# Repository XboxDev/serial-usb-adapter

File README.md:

# Original Xbox Serial USB Adapter

This device allows for serial communication with an original Xbox and is primarily used for kernel debugging.

For questions or support, contact xbox7887 in the [XboxDev on Discord](https://discord.gg/WxJPPyz).

## Requirements

### Hardware

Any original Xbox of any version (although versions 1.3-1.5 require LFRAME# reconnect and version 1.6 requires full LPC port rebuild, including LFRAME#).
Debug and development kits will work without modification, however, retail boxes need to use a hacked kernel (X2 5035 or Cerbios for example) that initializes superio as well as have a 2x8 2.54mm pin header soldered to the LPC port.

### Software

A Windows OS capable of running WinDbg; versions 4.0.0018.0 (XDK) or [6.12.0002.633](http://download.microsoft.com/download/A/6/A/A6AC035D-DA3F-4F0C-ADA4-37C8E5D34E3D/setup/WinSDKDebuggingTools/dbg_x86.msi) have been tested successfully.

Optionally, [KiCad 7.0](http://kicad-pcb.org/download/) if you need to work with the PCB project files.

### BIOS Compatibility

   - Cerbios - use on any board
   - X2 4979 BFM - use on any board
   - X2 4981 (256 KB) - use on 1.2+ boards
   - X2 4983 BFM - use on any board
   - X2 5035 (512 KB) - use on 1.0-1.1 boards

## Usage

Connect a USB-C cable from your PC to the serial adapter, then the IDC cable ends into the serial adapter and Xbox LPC port pin headers respectively, ensuring the correct alignment and orientation as shown in the image above. **Incorrect orientation may result in damage to the adapter and/or your Xbox, you have been warned!**

Within WinDbg press `CTRL+K` to bring up the connection dialog and enter `115200` for the baud rate along with the `COM#` port as detected by your computer in device manager.

`CTRL+Break` can be used to pause execution, `F5` to continue, and `F10/F11` to step over or through instructions.
`CTRL+ALT+D` will toggle verbose windbg protocol output for troubleshooting if needed.
The adapter's blue RX LED indicates signals sent from the PC and the green TX LED from the Xbox. 

## Components

Bold designators are the bare minimum required for basic functionality but stability may be questionable. The entire UART to USB circuit and/or LED output is optional and can be replaced with an external 3.3V UART to USB cable jumpered to J2 instead.

| Count | Part/Value | Description | Designators | Notes |
| - | - | - | - | - |
| 1  | 2x8 2.54mm | Pin Header | **JP1** | |
| 1  | Stewart SS-52400-003 | USB-C Connector  | **J1** | |
| 1  | 1x3 2.54mm | Pin Header | J2 | Optional UART breakout |
| 1  | SG5032CAN | 14.318MHz 5032 Crystal Oscillator | **Y1** | |
| 1  | LPC47M192 | SuperIO | **U1** | The LPC47M157 is also compatible |
| 1  | FT231XS | UART to USB | **U2** | |
| 2  | 27R | 0603 SMD Resistor | **R1**, **R3** | Filtering |
| 2  | 10k | 0603 SMD Resistor | **R2**, **R4** | Configuration pull-ups/downs |
| 1  | 470R | 0603 SMD Resistor | R5 | LED power dissipation |
| 1  | 1.2k | 0603 SMD Resistor | R6 | LED power dissipation  |
| 2  | 5.1k | 0603 SMD Resistor | **R7**, **R8** | USB-C Configuration pull-downs |
| 2  | 100R | 4x0603 SMD Resistor Network | **RN1**, **RN2** | Terminating resistors for longer LPC ribbons (10+ inches) |
| 1  | 33 Ohm | 0603 Ferrite Bead | **FB1** | Filtering, can be substituted with a 0 ohm resistor or solder bridge |
| 3  | 47pF | 0603 SMD Capacitor | C6, C7 | Filtering |
| 6  | 10nF | 0603 SMD Capacitor | C3, **C8**, C9, **C10**, C12, C13 | Decoupling |
| 2  | 100nF | 0603 SMD Capacitor | C2, C11 | Decoupling |
| 1  | 4.7uF | 0603 SMD Capacitor | C1 | Bulk |
| 1  | 10uF | 0603 SMD Capacitor | C5 | Bulk |
| 1  | Green | 0603 SMD LED | D1 | |
| 1  | Blue | 0603 SMD LED | D2 | |

### External Components

| Count | Part/Value | Description | Designators | Notes |
| - | - | - | - | - |
| 1 | 2x8 2.54mm | Pin Header | N/A | Retail Xbox LPC Connector |
| 1 | 16 Wire 2.54mm | Female to Female IDC Ribbon Cable | N/A | Keep length under 18 inches for best results |
| 1 | USB-C Cable | Cable | N/A | |

### Component Retailers

* [Mouser](https://www.mouser.com/)
* [Digi-Key](https://www.digikey.com/)
* [Arrow](https://www.arrow.com/)
* [Utsource](https://www.utsource.net/)
* [AliExpress](https://www.aliexpress.com/)
* [JLCPCB](https://jlcpcb.com/)

## Reference

## Copyright

Copyright Mike Davis 2019.

This documentation describes Open Hardware and is licensed under the
CERN OHL v. 1.2 or later.

You may redistribute and modify this documentation under the terms of the
CERN OHL v.1.2 or later. (http://ohwr.org/cernohl). This documentation is distributed
WITHOUT ANY EXPRESS OR IMPLIED WARRANTY, INCLUDING OF
MERCHANTABILITY, SATISFACTORY QUALITY AND FITNESS FOR A
PARTICULAR PURPOSE. Please see the CERN OHL v.1.2 or later for applicable
conditions

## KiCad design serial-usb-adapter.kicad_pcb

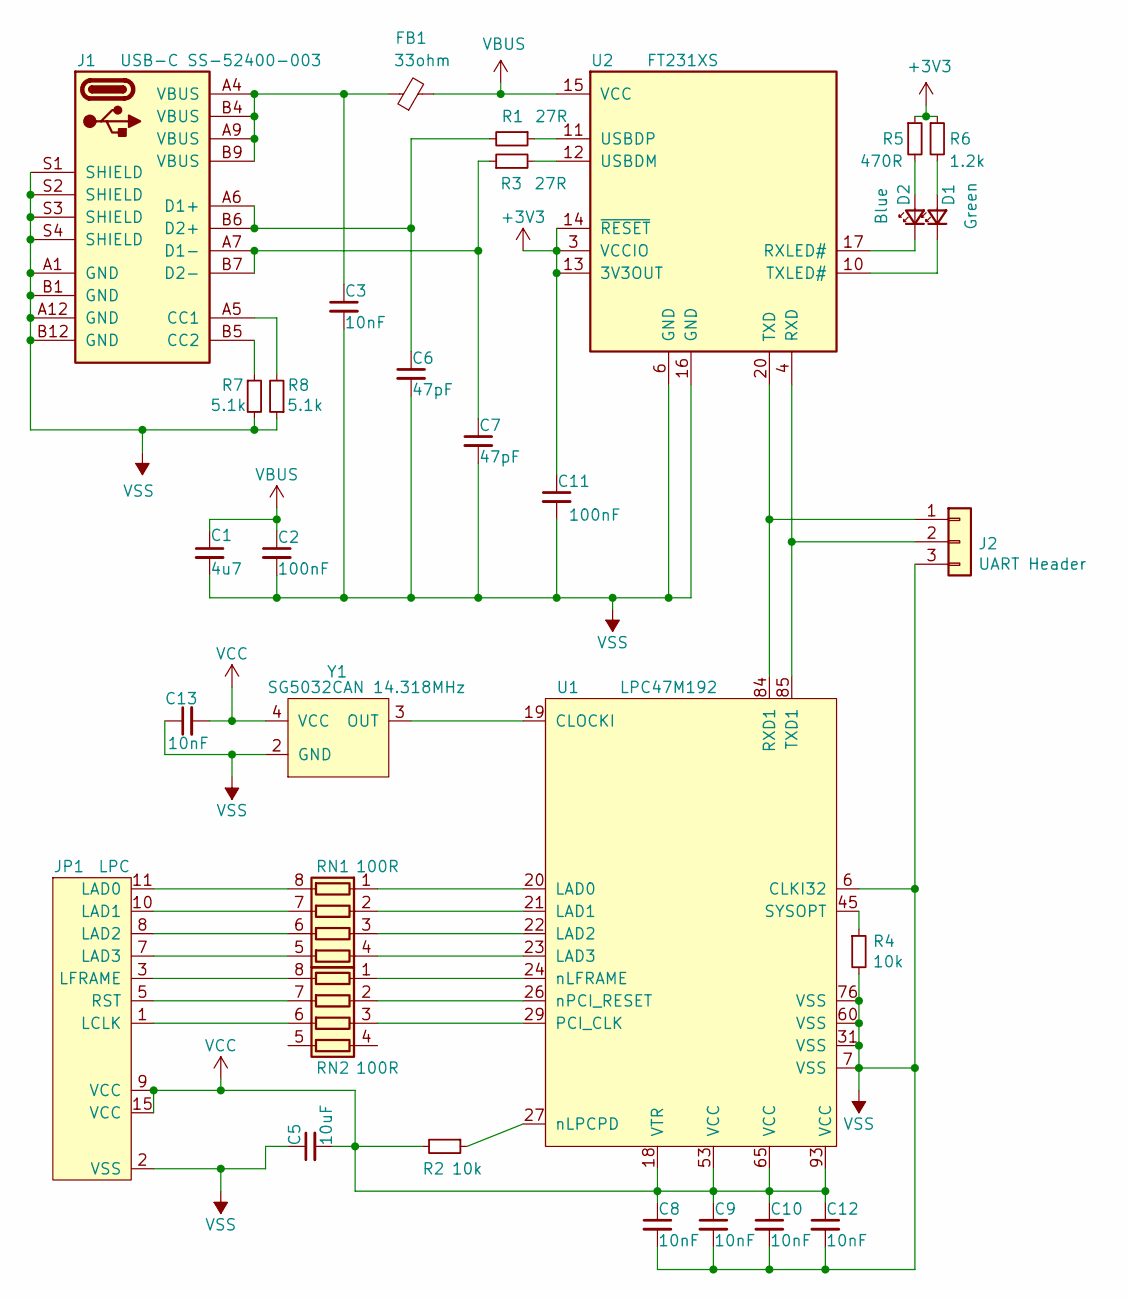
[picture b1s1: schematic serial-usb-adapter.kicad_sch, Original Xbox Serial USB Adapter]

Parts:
C1: 4u7; C_0603_1608Metric; LCSC C19666
C2, C11: 100nF; C_0603_1608Metric; LCSC C14663
C3, C8, C9, C10, C12, C13: 10nF; C_0603_1608Metric; LCSC C57112
C5: 10uF; C_0603_1608Metric; LCSC C19702
C6, C7: 47pF; C_0603_1608Metric; LCSC C1671
D1: Green; LED_0603_1608Metric; LCSC C72043
D2: Blue; LED_0603_1608Metric; LCSC C72041
FB1: 33ohm; L_0603_1608Metric; LCSC C88984
J1: USB-C SS-52400-003; SS-52400-003
J2: UART Header; PinHeader_1x03_P2.54mm_Vertical
JP1: LPC; PinHeader_2x08_P2.54mm_Vertical
R1, R3: 27R; R_0603_1608Metric; LCSC C25190
R2, R4: 10k; R_0603_1608Metric; LCSC C25804
R5: 470R; R_0603_1608Metric; LCSC C23179
R6: 1.2k; R_0603_1608Metric; LCSC C22765
R7, R8: 5.1k; R_0603_1608Metric; LCSC C25804
RN1, RN2: 100R; R_Array_Convex_4x0603; LCSC C79203
U1: LPC47M192; LQFP-128_14x20mm_P0.5mm
U2: FT231XS; SSOP-20_3.9x8.7mm_P0.635mm; LCSC C132160
Y1: SG5032CAN 14.318MHz; Oscillator_SMD_TXC_7C-4Pin_5.0x3.2mm_HandSoldering

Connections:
+3V3: C11.1, R5.1, R6.1, U2.3 (VCCIO), U2.13 (3V3OUT), U2.14 (~RESET)
unnamed: C3.1, FB1.1, J1.A4 (VBUS), J1.A9 (VBUS), J1.B4 (VBUS), J1.B9 (VBUS)
unnamed: C6.1, J1.A6 (D1+), J1.B6 (D2+), R1.2
unnamed: C7.1, J1.A7 (D1-), J1.B7 (D2-), R3.1
unnamed: D1.1 (K), U2.10 (TXLED#)
unnamed: D1.2 (A), R6.2
unnamed: D2.1 (K), U2.17 (RXLED#)
unnamed: D2.2 (A), R5.2
unnamed: J1.A5 (CC1), R8.2
unnamed: J1.B5 (CC2), R7.1
unnamed: J2.1 (TX), U1.84 (RXD1), U2.20 (TXD)
unnamed: J2.2 (RX), U1.85 (TXD1), U2.4 (RXD)
unnamed: JP1.1 (LCLK), RN2.6 (R3.2)
unnamed: JP1.3 (LFRAME), RN2.8 (R1.2)
unnamed: JP1.5 (RST), RN2.7 (R2.2)
unnamed: JP1.7 (LAD3), RN1.5 (R4.2)
unnamed: JP1.8 (LAD2), RN1.6 (R3.2)
unnamed: JP1.10 (LAD1), RN1.7 (R2.2)
unnamed: JP1.11 (LAD0), RN1.8 (R1.2)
unnamed: R1.1, U2.11 (USBDP)
unnamed: R2.1, U1.27 (nLPCPD)
unnamed: R3.2, U2.12 (USBDM)
unnamed: R4.1, U1.45 (SYSOPT)
unnamed: RN1.1 (R1.1), U1.20 (LAD0)
unnamed: RN1.2 (R2.1), U1.21 (LAD1)
unnamed: RN1.3 (R3.1), U1.22 (LAD2)
unnamed: RN1.4 (R4.1), U1.23 (LAD3)
unnamed: RN2.1 (R1.1), U1.24 (nLFRAME)
unnamed: RN2.2 (R2.1), U1.26 (nPCI_RESET)
unnamed: RN2.3 (R3.1), U1.29 (PCI_CLK)
unnamed: U1.19 (CLOCKI), Y1.3 (OUT)
VBUS: C1.1, C2.1, FB1.2, U2.15 (VCC)
VCC: C5.2, C8.1, C9.1, C10.1, C12.1, C13.2, JP1.9 (VCC), JP1.15 (VCC), R2.2, U1.18 (VTR), U1.53 (VCC), U1.65 (VCC), U1.93 (VCC), Y1.4 (VCC)
VSS: C1.2, C2.2, C3.2, C5.1, C6.2, C7.2, C8.2, C9.2, C10.2, C11.2, C12.2, C13.1, J1.A1 (GND), J1.A12 (GND), J1.B1 (GND), J1.B12 (GND), J1.S1 (SHIELD), J1.S2 (SHIELD), J1.S3 (SHIELD), J1.S4 (SHIELD), J2.3 (GND), JP1.2 (VSS), R4.2, R7.2, R8.1, U1.6 (CLKI32), U1.7 (VSS), U1.31 (VSS), U1.60 (VSS), U1.76 (VSS), U2.6 (GND), U2.16 (GND), Y1.2 (GND)

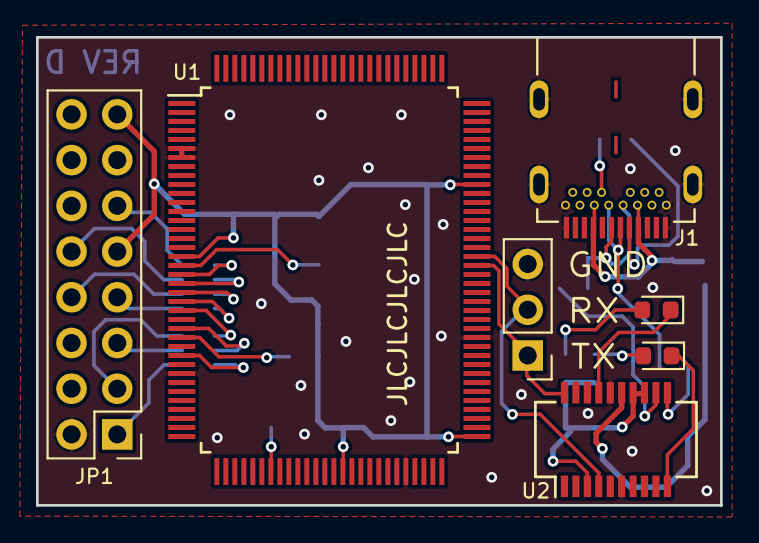
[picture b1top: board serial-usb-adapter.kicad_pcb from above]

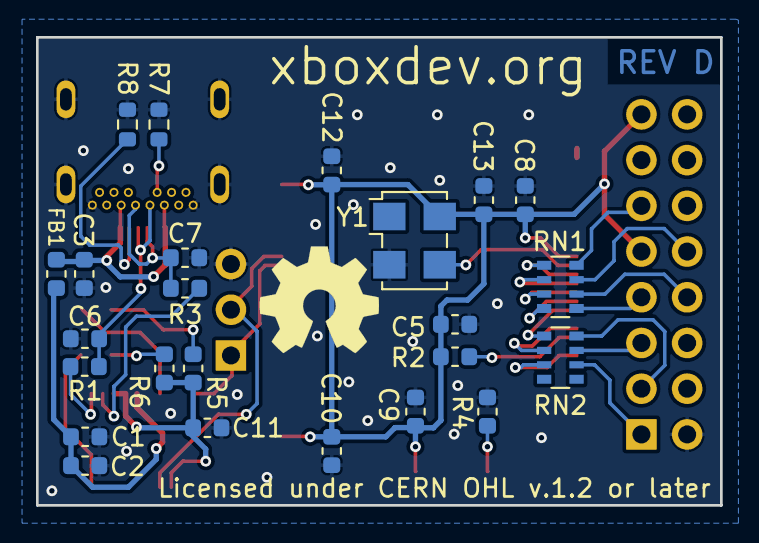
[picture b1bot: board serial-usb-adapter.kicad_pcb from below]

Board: 2 copper layers, 38.0 x 26.0 mm, 31 parts (24 on the bottom side), 34 nets.

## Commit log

2019-03-30 Initial Rev B commit
2019-06-26 Pin header pitch correction in README.md
2019-07-25 pin pitch & resistor value correction
2019-07-25 swap silkscreen positions of R1 & R3
2022-04-04 Replace Mini USB connector with Micro USB
2023-08-13 Adds USB-C based Xbox Serial USB Adapter (Rev D)

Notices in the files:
serial-usb-adapter.kicad_pcb:
Licensed under CERN OHL v.1.2 or later
